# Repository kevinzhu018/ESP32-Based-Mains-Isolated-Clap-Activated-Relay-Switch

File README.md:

ESP32-Based Mains-Isolated Clap-Activated Relay Switch

Custom KiCad PCB integrating an analog microphone front-end, ESP32-C6 processing, and a transistor-driven relay stage to safely switch a 120VAC load.

Includes schematic, PCB layout, BOM, and custom symbols/footprints.

⚠ This project involves mains voltage and should be handled with proper safety precautions.

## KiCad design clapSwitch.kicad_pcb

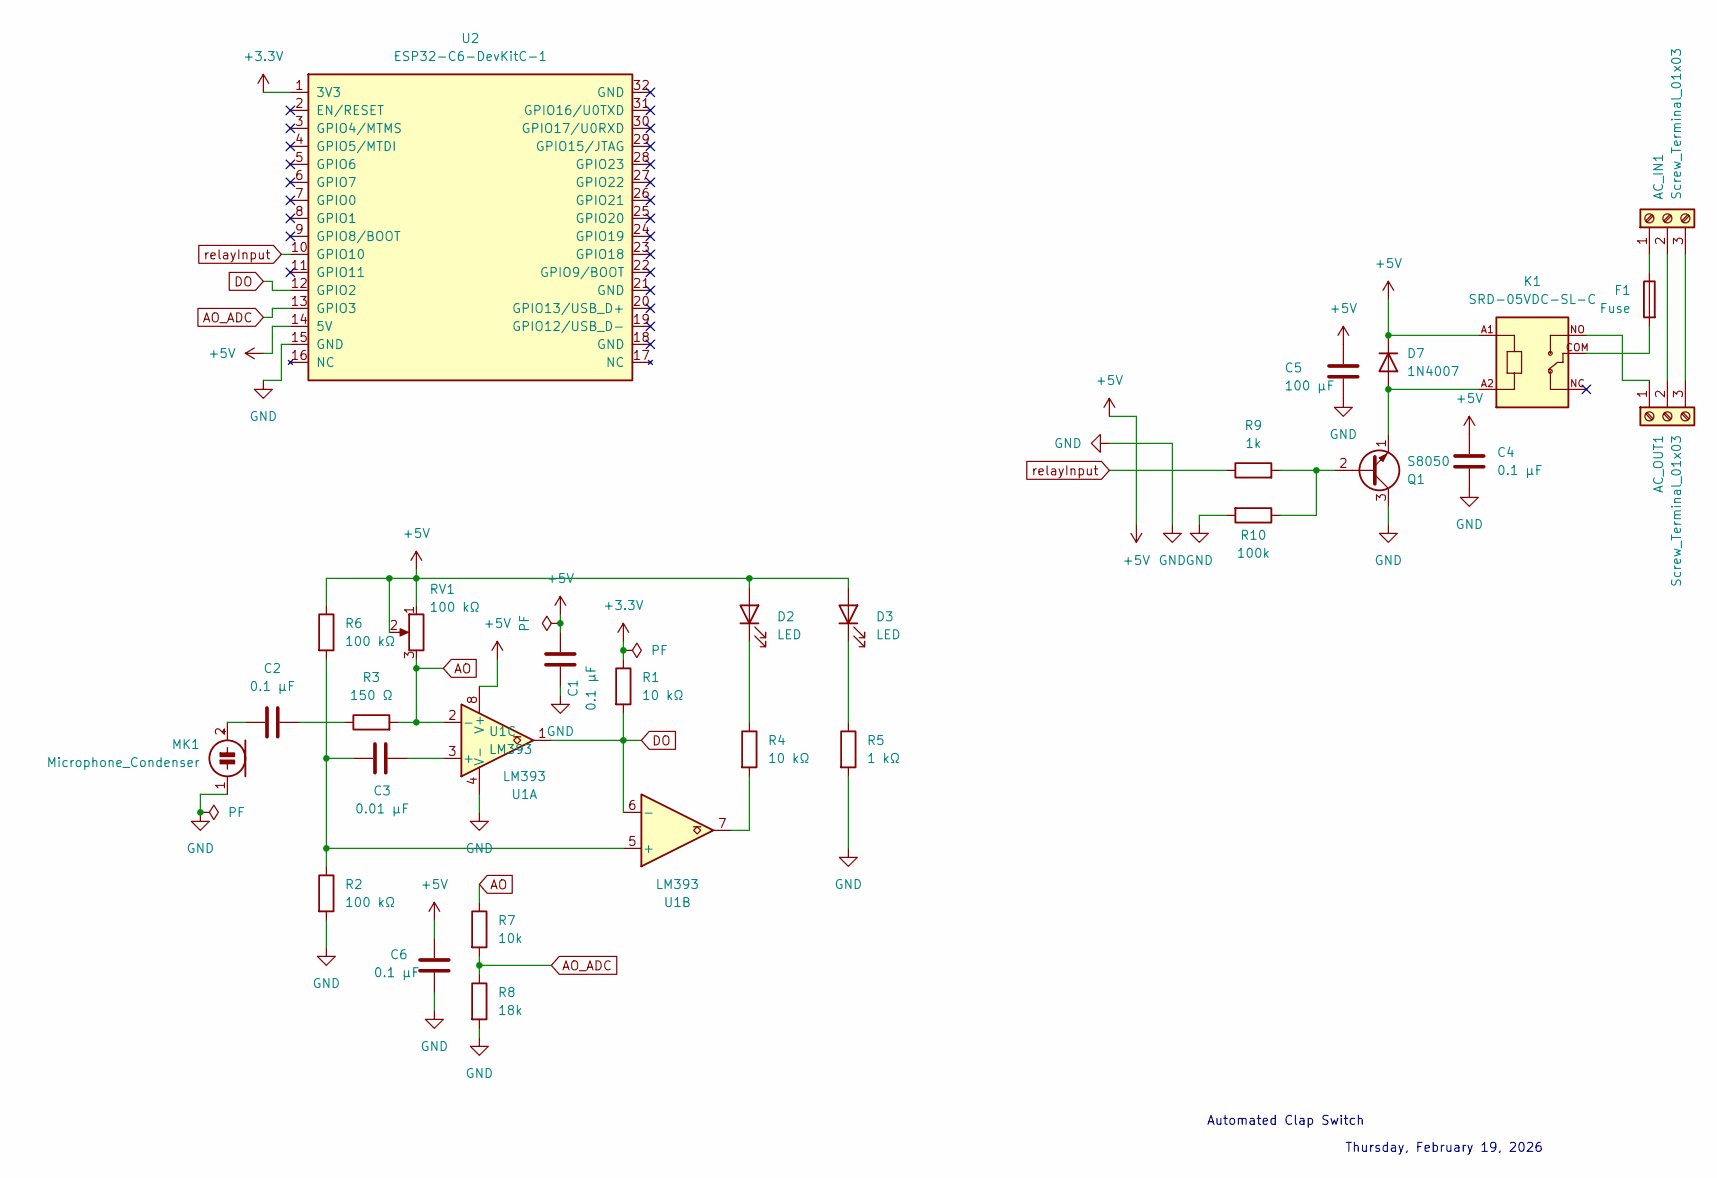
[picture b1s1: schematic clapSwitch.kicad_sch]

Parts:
AC_IN1: Screw_Terminal_01x03; TerminalBlock_MaiXu_MX126-5.0-03P_1x03_P5.00mm
AC_OUT1: Screw_Terminal_01x03; TerminalBlock_MaiXu_MX126-5.0-03P_1x03_P5.00mm
C1, C2, C4: 0.1 µF; C_0805_2012Metric
C3: 0.01 µF; C_0805_2012Metric
C5: 100 µF; CP_Radial_D8.0mm_P3.50mm
C6: 0.1 μF; C_0805_2012Metric
D2, D3: LED; LED_0805_2012Metric
D7: 1N4007; D_DO-41_SOD81_P7.62mm_Horizontal
F1: Fuse; Fuseholder_Clip-5x20mm_Littelfuse_111_Inline_P20.00x5.00mm_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
K1: SRD-05VDC-SL-C; RELAY_SRD-05VDC-SL-C
MK1: Microphone_Condenser; CUI_CMC-4013-SMT
Q1: S8050; SOT-23
R1, R4: 10 kΩ; R_0805_2012Metric
R2, R6: 100 kΩ; R_0805_2012Metric
R3: 150 Ω; R_0805_2012Metric
R5: 1 kΩ; R_0805_2012Metric
R7: 10k; R_0805_2012Metric
R8: 18k; R_0805_2012Metric
R9: 1k; R_0805_2012Metric
R10: 100k; R_0805_2012Metric
RV1: 100 kΩ; Potentiometer_Bourns_3296W_Vertical
U1: LM393; SOIC-8_3.9x4.9mm_P1.27mm
U2: ESP32-C6-DevKitC-1

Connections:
+3.3V: R1.1, U2.1 (3V3)
+5V: C1.2, C4.1, C5.1, C6.1, D2.2 (A), D3.2 (A), D7.1 (K), K1.A1, R6.1, RV1.1, RV1.2, U1.8 (V+), U2.14 (5V)
AO: R3.2, R7.1, RV1.3, U1.2 (-)
AO_ADC: R7.2, R8.1, U2.13 (GPIO3)
DO: R1.2, U1.1, U1.6 (-), U2.12 (GPIO2)
GND: C1.1, C4.2, C5.2, C6.2, MK1.1 (-), Q1.3 (C), R2.2, R5.2, R8.2, R10.2, U1.4 (V-), U2.15 (GND)
unnamed: AC_IN1.1, F1.1
unnamed: AC_IN1.2, AC_OUT1.2
unnamed: AC_IN1.3, AC_OUT1.3
unnamed: AC_OUT1.1, K1.NO
unnamed: C2.2, R3.1
unnamed: D2.1 (K), R4.1
unnamed: D3.1 (K), R5.1
unnamed: D7.2 (A), K1.A2, Q1.1 (E)
unnamed: F1.2, K1.COM
unnamed: C2.1, MK1.2 (+)
unnamed: Q1.2 (B), R9.2, R10.1
unnamed: R4.2, U1.7
unnamed: C3.2, U1.3 (+)
unnamed: C3.1, R2.1, R6.2, U1.5 (+)
relayInput: R9.1, U2.10 (GPIO10)

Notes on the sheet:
Thursday, February 19, 2026
Automated Clap Switch

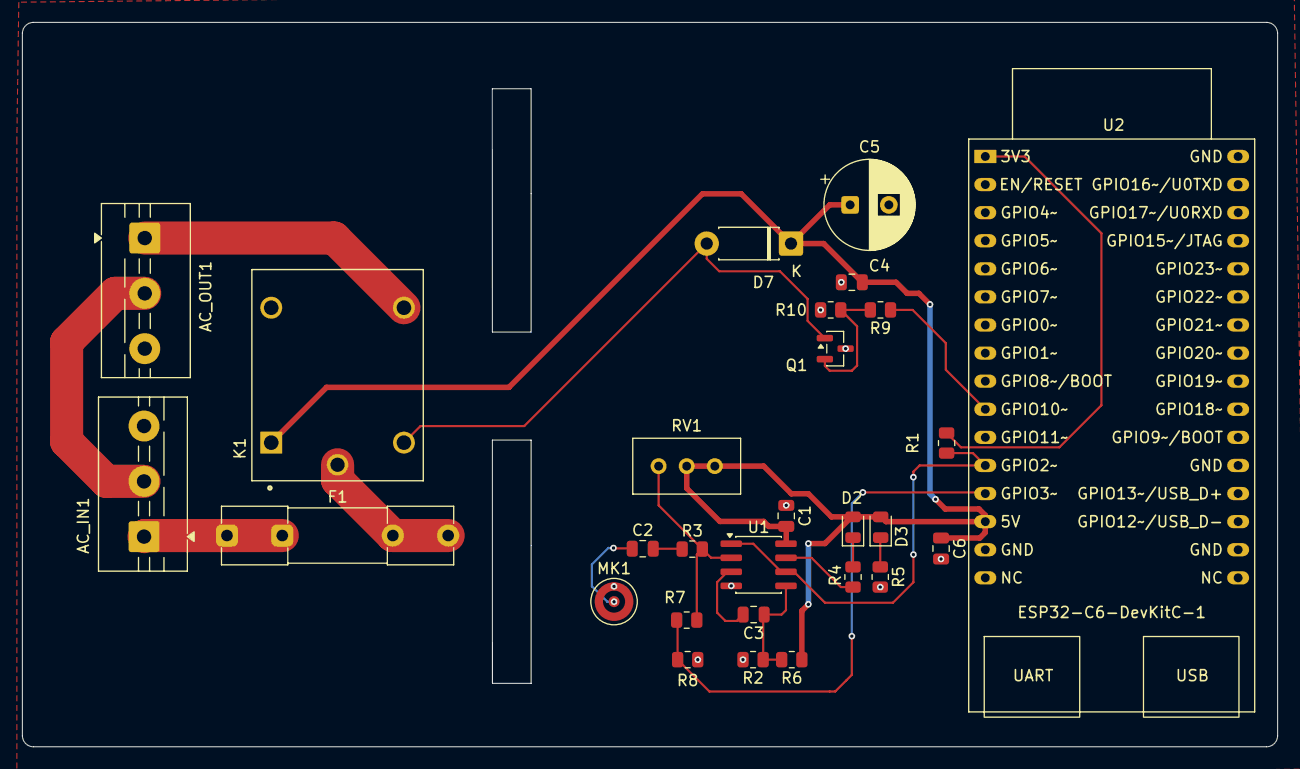
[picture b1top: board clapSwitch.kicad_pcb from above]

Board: 2 copper layers, 113.5 x 65.5 mm, 28 parts (0 on the bottom side), 21 nets.

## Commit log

2026-02-22 Design V1
2026-02-22 Relevant symbols and footprints
    ""
2026-02-22 Bill of Matierals
2026-02-22 Conceptual flowchart depicting system
2026-02-22 Project description
